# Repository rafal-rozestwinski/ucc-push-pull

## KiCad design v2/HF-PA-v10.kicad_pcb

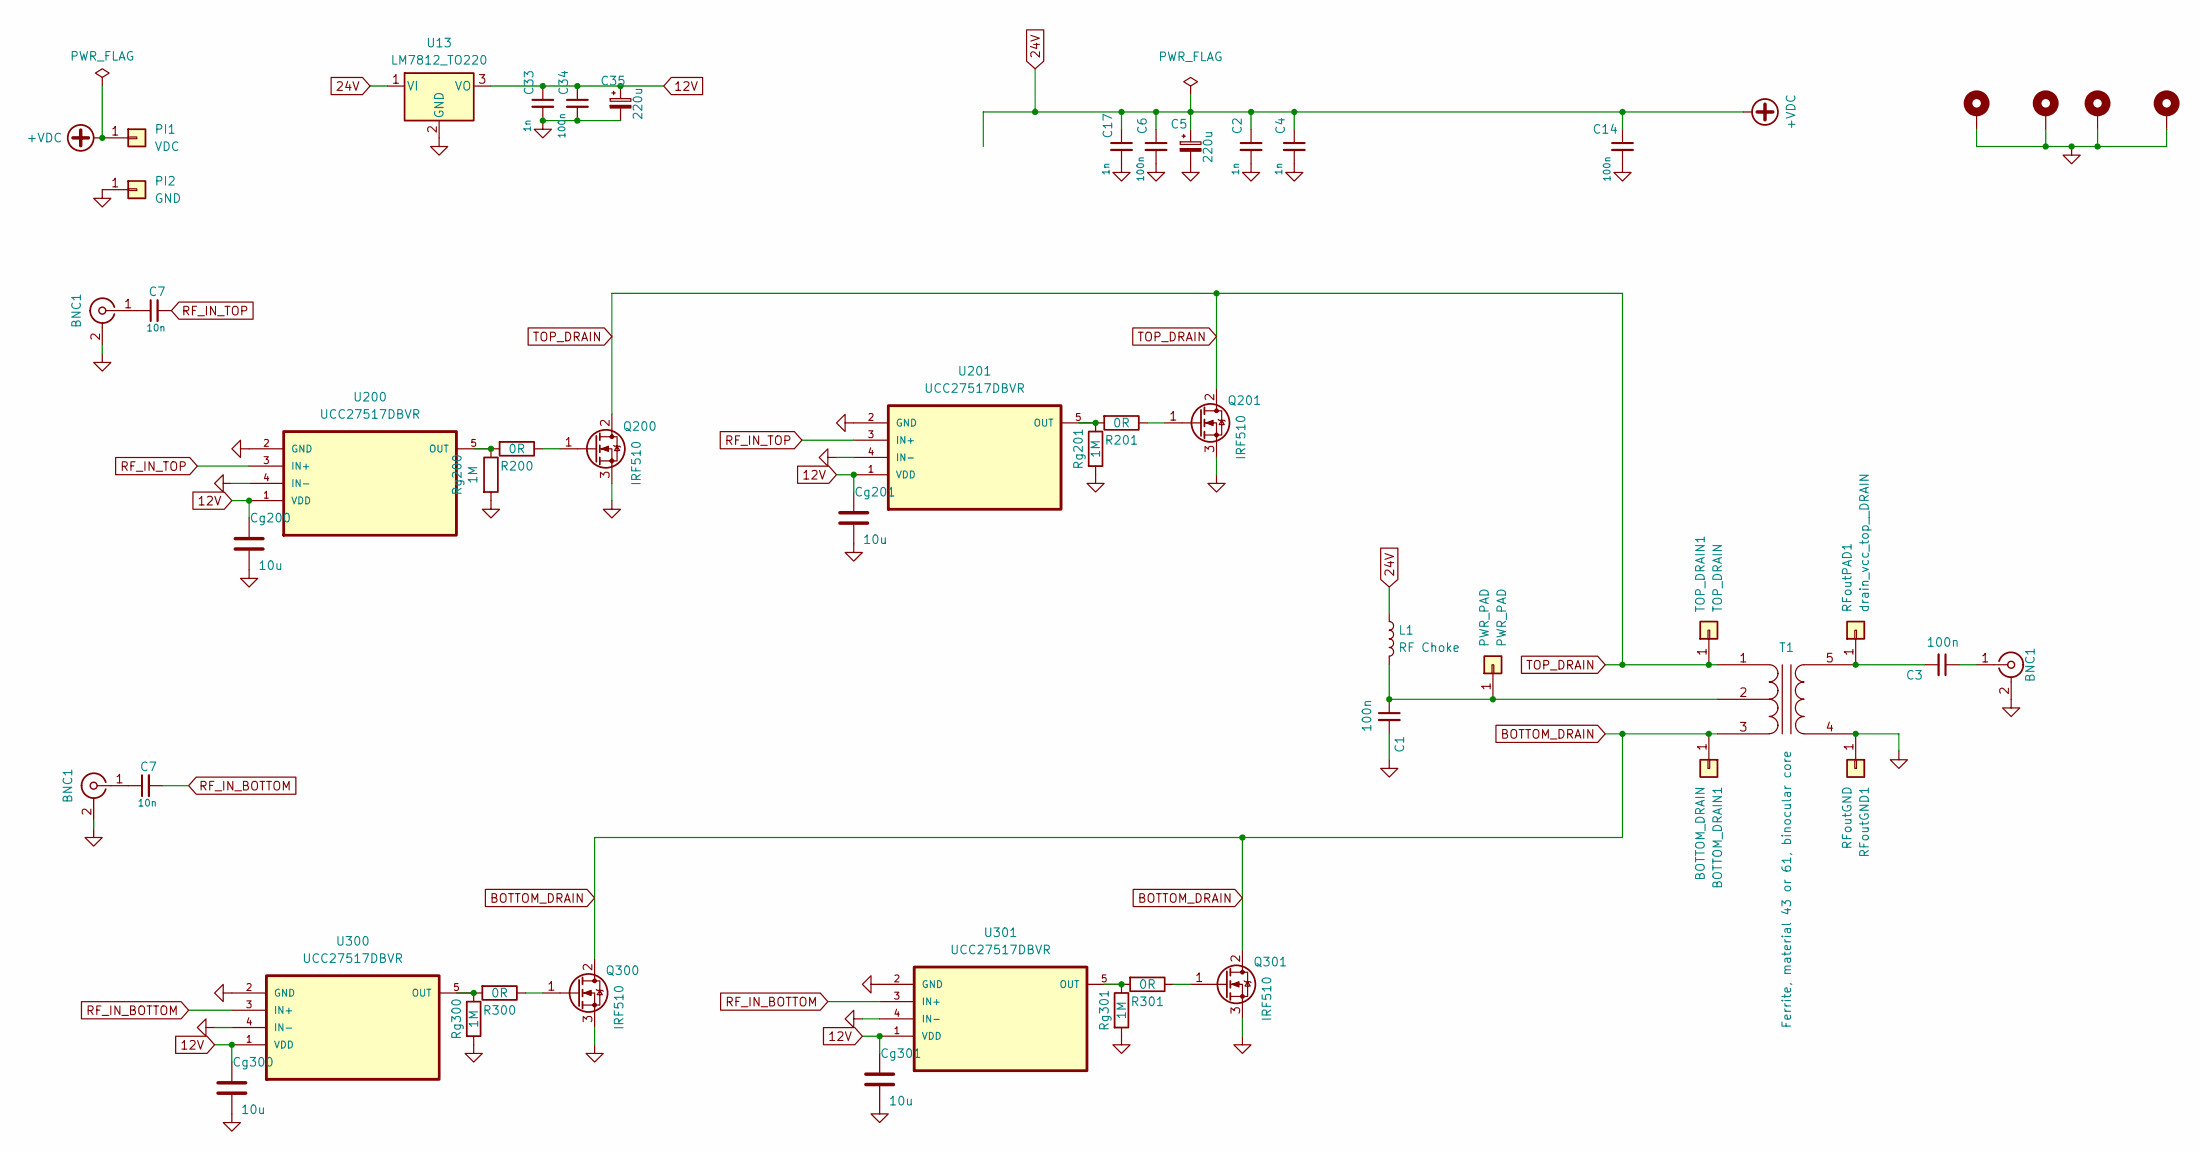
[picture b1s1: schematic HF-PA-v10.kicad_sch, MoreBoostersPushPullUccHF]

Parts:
BNC1: SMA; SMA_Samtec_SMA-J-P-X-ST-EM1_EdgeMount
BOTTOM_DRAIN1: BOTTOM_DRAIN; TestPoint_Pad_4.0x4.0mm
C1, C3, C6, C14, C34: 100n; C_1206_3216Metric_Pad1.33x1.80mm_HandSolder
C2, C4, C17, C33: 1n; C_1206_3216Metric_Pad1.33x1.80mm_HandSolder
C5, C35: 220u; CP_Elec_8x10.5
C7: 10n; C_1206_3216Metric_Pad1.33x1.80mm_HandSolder
Cg200, Cg201, Cg300, Cg301: 10u; C_1206_3216Metric_Pad1.33x1.80mm_HandSolder
H1, H2, H3, H4: MountingHole_Pad; MountingHole_3.2mm_M3_Pad
L1: RF Choke; L_Sumida_CDMC6D28_7.25x6.5mm
PI1: VDC; TestPoint_Pad_4.0x4.0mm
PI2: GND; TestPoint_Pad_4.0x4.0mm
PWR_PAD: PWR_PAD; TestPoint_Pad_4.0x4.0mm
Q200, Q201, Q300, Q301: IRF510; SO2A_TO-220-3_Horizontal_TabDown
R200, R201, R300, R301: 0R; R_2512_6332Metric_Pad1.40x3.35mm_HandSolder
RFoutGND1: RFoutGND; TestPoint_Pad_4.0x4.0mm
RFoutPAD1: drain_vcc_top__DRAIN; TestPoint_Pad_4.0x4.0mm
Rg200, Rg201, Rg300, Rg301: 1M; R_1206_3216Metric_Pad1.30x1.75mm_HandSolder
T1: Ferrite, material 43 or 61, binocular core
TOP_DRAIN1: TOP_DRAIN; TestPoint_Pad_4.0x4.0mm
U13: LM7812_TO220; TO-220-3_Vertical
U200, U201, U300, U301: UCC27517DBVR; SOT-23-5_HandSoldering

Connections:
12V: C33.1, C34.1, C35.1, Cg200.1, Cg201.1, Cg300.1, Cg301.1, U13.3 (VO), U200.1 (VDD), U201.1 (VDD), U300.1 (VDD), U301.1 (VDD)
24V: C2.1, C4.1, C5.1, C6.1, C14.1, C17.1, L1.1, PI1.1, U13.1 (VI)
BOTTOM_DRAIN: BOTTOM_DRAIN1.1, Q300.2 (D), Q301.2 (D), T1.3 (PR2)
unnamed 3: C3.1; also elsewhere on the board
unnamed 4: C1.1, L1.2, PWR_PAD.1, T1.2 (PM); also elsewhere on the board
unnamed: Q200.1 (G), R200.1
unnamed: Q201.1 (G), R201.1
unnamed: Q300.1 (G), R300.1
unnamed: Q301.1 (G), R301.1
unnamed: C3.2, RFoutPAD1.1, T1.5 (S2)
unnamed: R200.2, Rg200.1, U200.5 (OUT)
unnamed: R201.2, Rg201.1, U201.5 (OUT)
unnamed: R300.2, Rg300.1, U300.5 (OUT)
unnamed: R301.2, Rg301.1, U301.5 (OUT)
RF_IN_BOTTOM: U300.3 (IN+), U301.3 (IN+); also elsewhere on the board
RF_IN_TOP: U200.3 (IN+), U201.3 (IN+); also elsewhere on the board
TOP_DRAIN: Q200.2 (D), Q201.2 (D), T1.1 (PR1), TOP_DRAIN1.1

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
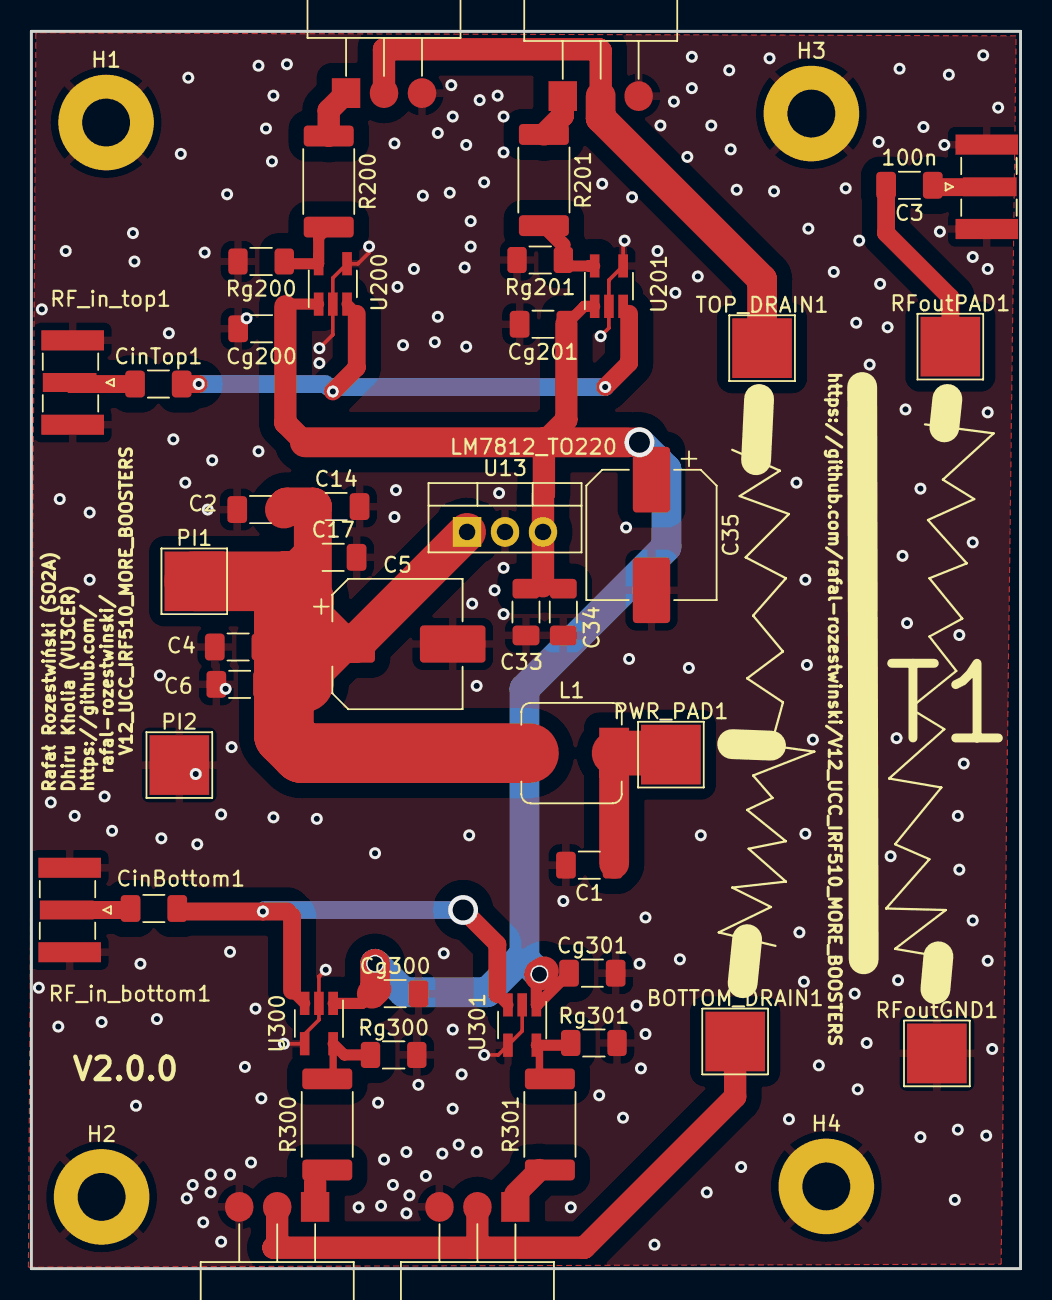
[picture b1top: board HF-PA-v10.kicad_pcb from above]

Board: 2 copper layers, 66.2 x 82.8 mm, 49 parts (0 on the bottom side), 20 nets.

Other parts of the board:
BNC2: SMA; SMA_Samtec_SMA-J-P-X-ST-EM1_EdgeMount
CinBottom1: 10n; C_1206_3216Metric_Pad1.33x1.80mm_HandSolder
CinTop1: 10n; C_1206_3216Metric_Pad1.33x1.80mm_HandSolder
PWR_PAD1: PWR_PAD; TestPoint_Pad_4.0x4.0mm
RF_in_bottom1: SMA; SMA_Samtec_SMA-J-P-X-ST-EM1_EdgeMount
RF_in_top1: SMA; SMA_Samtec_SMA-J-P-X-ST-EM1_EdgeMount

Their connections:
unnamed 3: BNC2.1 (In); also elsewhere on the board
unnamed 4: PWR_PAD1.1; also elsewhere on the board
unnamed: CinBottom1.1, RF_in_bottom1.1 (In)
unnamed: CinTop1.1, RF_in_top1.1 (In)
RF_IN_BOTTOM: CinBottom1.2; also elsewhere on the board
RF_IN_TOP: CinTop1.2; also elsewhere on the board

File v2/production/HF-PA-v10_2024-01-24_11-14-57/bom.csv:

Designator,Footprint,Quantity,Value,LCSC Part #
"BNC2, RF_in_bottom1, RF_in_top1",SMA_Samtec_SMA-J-P-X-ST-EM1_EdgeMount,3,SMA,
BOTTOM_DRAIN1,TestPoint_Pad_4.0x4.0mm,1,BOTTOM_DRAIN,
"C1, C14, C3, C34, C6",1206,5,100n,
"C17, C2, C33, C4",1206,4,1n,
"C35, C5",CP_Elec_8x10.5,2,220u,
"Cg200, Cg201, Cg300, Cg301",1206,4,10u,
"CinBottom1, CinTop1",1206,2,10n,
"H1, H2, H3, H4",MountingHole_3.2mm_M3_Pad,4,MountingHole_Pad,
L1,L_Sumida_CDMC6D28_7.25x6.5mm,1,RF Choke,
PI1,TestPoint_Pad_4.0x4.0mm,1,VDC,
PI2,TestPoint_Pad_4.0x4.0mm,1,GND,
PWR_PAD1,TestPoint_Pad_4.0x4.0mm,1,PWR_PAD,
"Q200, Q201, Q300, Q301",SO2A_TO-220-3_Horizontal_TabDown,4,IRF510,
"R200, R201, R300, R301",2512,4,0R,
RFoutGND1,TestPoint_Pad_4.0x4.0mm,1,RFoutGND,
RFoutPAD1,TestPoint_Pad_4.0x4.0mm,1,drain_vcc_top__DRAIN,
"Rg200, Rg201, Rg300, Rg301",1206,4,1M,
TOP_DRAIN1,TestPoint_Pad_4.0x4.0mm,1,TOP_DRAIN,
U13,TO-220-3_Vertical,1,LM7812_TO220,
"U200, U201, U300, U301",SOT-23-5_HandSoldering,4,UCC27517DBVR,
